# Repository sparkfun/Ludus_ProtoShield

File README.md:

**NOTE:** *This product has been retired from our catalog. If you are looking for more up-to-date info, please check out some of these resources to see how other users are still hacking and improving on this product.*
* *[SparkFun Forum](https://forum.sparkfun.com/)*
* *[Comments Here on GitHub](https://github.com/sparkfun/Ludus_ProtoShield/issues)*
* *[IRC Channel](https://www.sparkfun.com/news/263)*

SparkFun Ludus ProtoShield
===========================

[*SparkFun Ludus ProtoShield (DEV-13310)*](https://www.sparkfun.com/products/13310)

This is an Arduino shield that integrates an H-Bridge Driver and breaks out 
all I/O ports to three-pin headers on a GND / PWR / SIG standard. This enables quick
prototyping and integration of Arduino projects w/o the need of a breadboard.

Ludus is the mascot of the SparkFun Education team. It is a highly intelligent octopus.

                   _,--._
                      ,'      `.
              |\     / ,-.  ,-. \     /|
              )o),/ ( ( o )( o ) ) \.(o(
             /o/// /|  `-'  `-'  |\ \\\o\
            / / |\ \(   .    ,   )/ /| \ \
            | | \o`-/    `\/'    \-'o/ | |
            \ \  `,'              `.'  / /
         \.  \ `-'  ,'|   /\   |`.  `-' /  ,/
          \`. `.__,' /   /  \   \ `.__,' ,'/
           \o\     ,'  ,'    `.  `.     /o/
            \o`---'  ,'        `.  `---'o/
             `.____,'  -shimrod  `.____,'

Repository Contents
-------------------

* **/Firmware** - Example code 
* **/Hardware** - Eagle design files (.brd, .sch)
* **/Production** - Production panel files (.brd)

Documentation
--------------
* **[Hookup Guide](https://learn.sparkfun.com/tutorials/ludus-protoshield-hookup-guide)** - Basic hookup guide for the Ludus ProtoShield.
* **[SparkFun Fritzing repo](https://github.com/sparkfun/Fritzing_Parts)** - Fritzing diagrams for SparkFun products.
* **[SparkFun 3D Model repo](https://github.com/sparkfun/3D_Models)** - 3D models of SparkFun products. 

License Information
-------------------

This product is _**open source**_! 

Please review the LICENSE.md file for license information. 

If you have any questions or concerns on licensing, please contact techsupport@sparkfun.com.

Distributed as-is; no warranty is given.

- Your friends at SparkFun.

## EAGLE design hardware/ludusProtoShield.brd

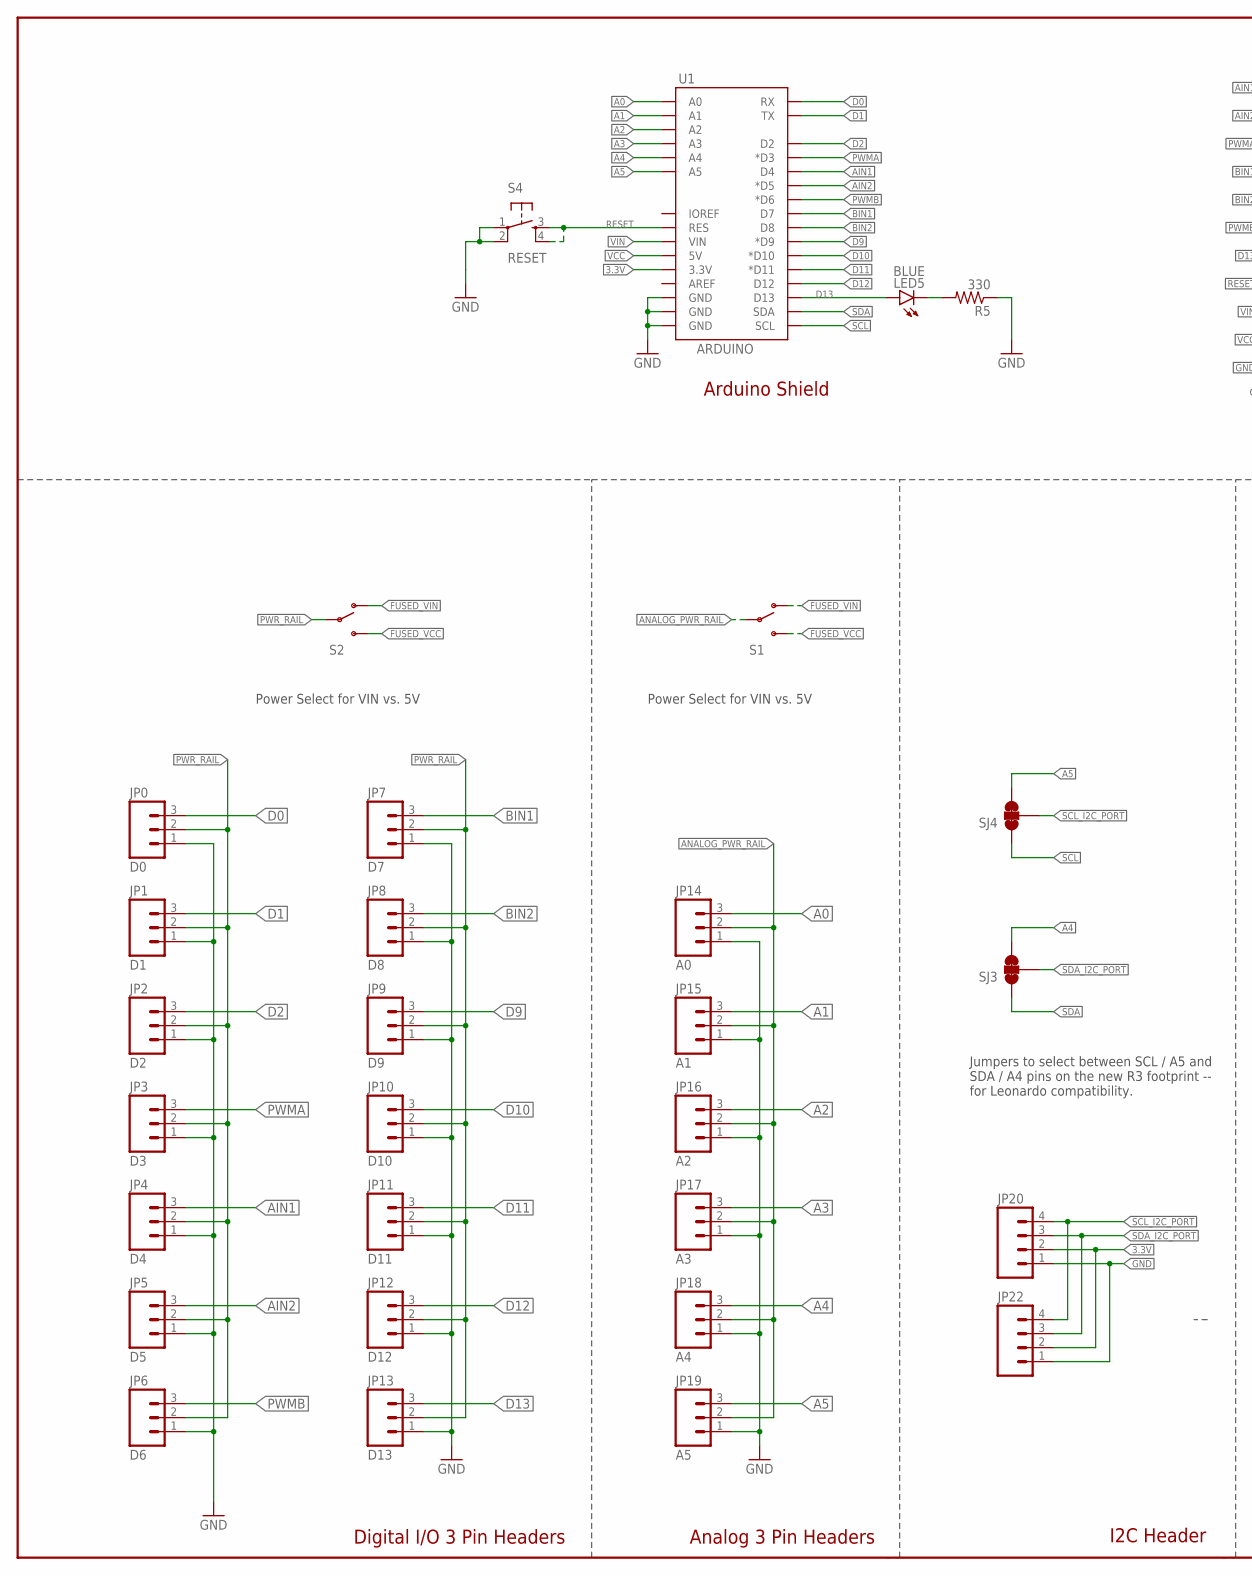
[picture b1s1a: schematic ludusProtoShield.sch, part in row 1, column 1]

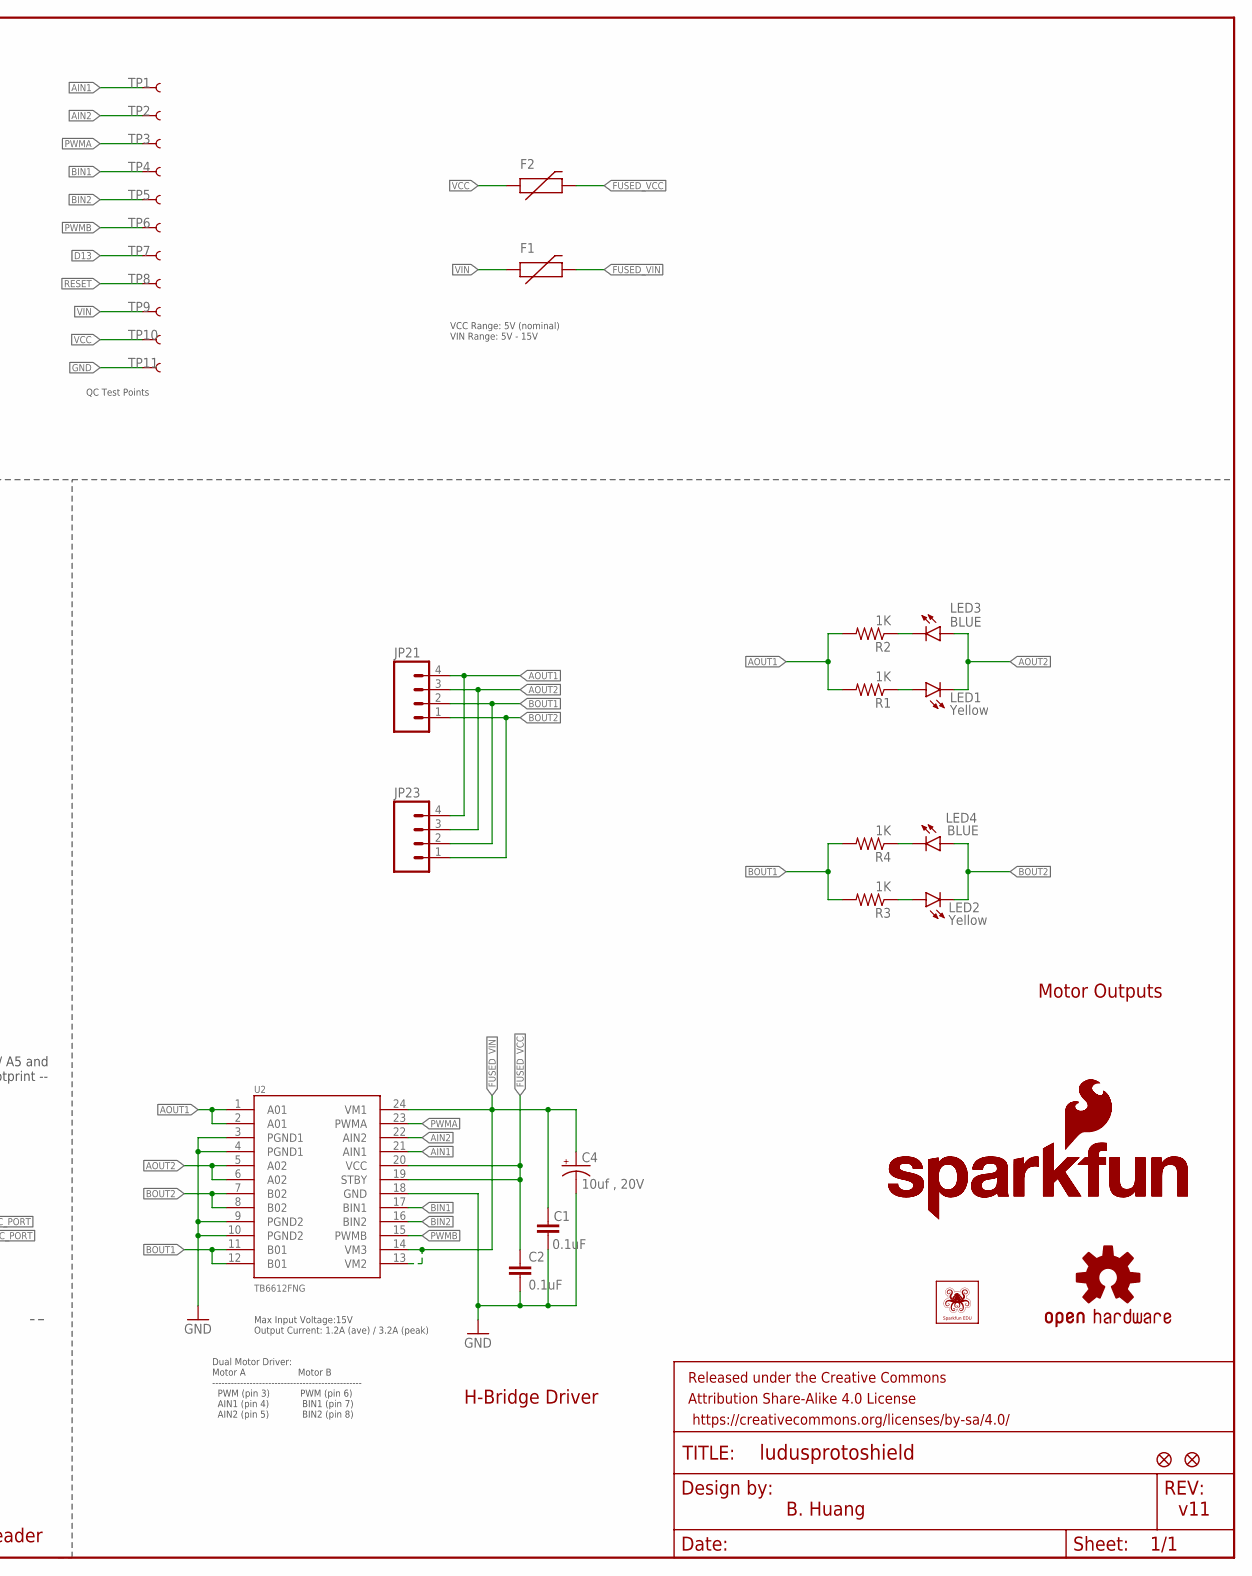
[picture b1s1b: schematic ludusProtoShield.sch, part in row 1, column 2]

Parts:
C1, C2: 0.1uF; 0603-CAP
C4: 10uf , 20V; EIA3528
F1, F2: PTCSMD; PTC-1206
FID1, FID2: FIDUCIAL1X2; FIDUCIAL-1X2
FRAME2: FRAME-LEDGER; CREATIVE_COMMONS
JP0: D0; 1X03_LOCK
JP1: D1; 1X03_LOCK
JP2: D2; 1X03_LOCK
JP3: D3; 1X03_LOCK
JP4: D4; 1X03_LOCK
JP5: D5; 1X03_LOCK
JP6: D6; 1X03_LOCK
JP7: D7; 1X03_LOCK
JP8: D8; 1X03_LOCK
JP9: D9; 1X03_LOCK
JP10: D10; 1X03_LOCK
JP11: D11; 1X03_LOCK
JP12: D12; 1X03_LOCK
JP13: D13; 1X03_LOCK
JP14: A0; 1X03_LOCK
JP15: A1; 1X03_LOCK
JP16: A2; 1X03_LOCK
JP17: A3; 1X03_LOCK
JP18: A4; 1X03_LOCK
JP19: A5; 1X03_LOCK
JP20, JP21: M04PTH; 1X04
JP22, JP23: M04LOCK; 1X04_LOCK
LED1, LED2: Yellow; LED-0603
LED3, LED4, LED5: BLUE; LED-0603
LOGO1: OSHW-LOGOM; OSHW-LOGO-M
LOGO2, LOGO4: SFE_LOGO_NAME_FLAME.1_INCH; SFE_LOGO_NAME_FLAME_.1
LOGO3: SFE_LOGO_FLAME.2COP; SFE_LOGO_FLAME_COPPER_.2
R1, R2, R3, R4: 1K; 0603-RES
R5: 330; 0603-RES
S1, S2: SWITCH-SPDTSMD; AYZ0202
S4: RESET; TACTILE-SWITCH-SMD
SJ3, SJ4: JUMPER-PAD-3-NC_BY_TRACE; PAD-JUMPER-3-3OF3_NC_BY_TRACE_YES_SILK_FULL_BOX
TP1, TP2, TP3, TP4, TP5, TP6, TP7, TP8, TP9, TP10, TP11: TEST-POINT3X5; PAD.03X.05
U1: ARDUINO; UNO_R3_SHIELD_NOLABELS_LOCK
U2: TB6612FNG; SSOP24
U$1: SFE_LUDUSSFE_LUDUS-M; SFE_LUDUS-M

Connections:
3.3V: JP20.2, JP22.2, U1.3.3V
A0: JP14.3, U1.A0
A1: JP15.3, U1.A1
A2: JP16.3, U1.A2
A3: JP17.3, U1.A3
A4: JP18.3, SJ3.3, U1.A4
A5: JP19.3, SJ4.3, U1.A5
AIN1: JP4.3, TP1.P$1, U1.D4, U2.21 (AIN1)
AIN2: JP5.3, TP2.P$1, U1.D5 (*D5), U2.22 (AIN2)
ANALOG_PWR_RAIL: JP14.2, JP15.2, JP16.2, JP17.2, JP18.2, JP19.2, S1.2
AOUT1: JP21.4, JP23.4, R1.2, R2.2, U2.1 (A01), U2.2 (A01)
AOUT2: JP21.3, JP23.3, LED1.C, LED3.A, U2.5 (A02), U2.6 (A02)
BIN1: JP7.3, TP4.P$1, U1.D7, U2.17 (BIN1)
BIN2: JP8.3, TP5.P$1, U1.D8, U2.16 (BIN2)
BOUT1: JP21.2, JP23.2, R3.2, R4.2, U2.11 (B01), U2.12 (B01)
BOUT2: JP21.1, JP23.1, LED2.C, LED4.A, U2.7 (B02), U2.8 (B02)
D0: JP0.3, U1.RX
D1: JP1.3, U1.TX
D2: JP2.3, U1.D2
D9: JP9.3, U1.D9 (*D9)
D10: JP10.3, U1.D10 (*D10)
D11: JP11.3, U1.D11 (*D11)
D12: JP12.3, U1.D12
D13: JP13.3, LED5.A, TP7.P$1, U1.D13
FUSED_VCC: C2.1, F2.2, S1.3 (S), S2.3 (S), U2.19 (STBY), U2.20 (VCC)
FUSED_VIN: C1.1, C4.A (+), F1.2, S1.1 (O), S2.1 (O), U2.13 (VM2), U2.14 (VM3), U2.24 (VM1)
GND: C1.2, C2.2, C4.C (-), JP0.1, JP1.1, JP2.1, JP3.1, JP4.1, JP5.1, JP6.1, JP7.1, JP8.1, JP9.1, JP10.1, JP11.1, JP12.1, JP13.1, JP14.1, JP15.1, JP16.1, JP17.1, JP18.1, JP19.1, JP20.1, JP22.1, R5.1, S4.1, S4.2, TP11.P$1, U1.GND@0 (GND), U1.GND@1 (GND), U1.GND@2 (GND), U2.3 (PGND1), U2.4 (PGND1), U2.9 (PGND2), U2.10 (PGND2), U2.18 (GND)
unnamed: LED5.C, R5.2
unnamed: LED1.A, R1.1
unnamed: LED3.C, R2.1
unnamed: LED2.A, R3.1
unnamed: LED4.C, R4.1
PWMA: JP3.3, TP3.P$1, U1.D3 (*D3), U2.23 (PWMA)
PWMB: JP6.3, TP6.P$1, U1.D6 (*D6), U2.15 (PWMB)
PWR_RAIL: JP0.2, JP1.2, JP2.2, JP3.2, JP4.2, JP5.2, JP6.2, JP7.2, JP8.2, JP9.2, JP10.2, JP11.2, JP12.2, JP13.2, S2.2
RESET: S4.3, S4.4, TP8.P$1, U1.RES
SCL: SJ4.1, U1.SCL
SCL_I2C_PORT: JP20.4, JP22.4, SJ4.2
SDA: SJ3.1, U1.SDA
SDA_I2C_PORT: JP20.3, JP22.3, SJ3.2
VCC: F2.1, TP10.P$1, U1.5V
VIN: F1.1, TP9.P$1, U1.VIN

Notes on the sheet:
Arduino Shield
H-Bridge Driver
I2C Header
Motor Outputs
B. Huang
v11
Digital I/O 3 Pin Headers
Analog 3 Pin Headers
Jumpers to select between SCL / A5 and SDA / A4 pins on the new R3 footprint -- for Leonardo compatibility.
Power Select for VIN vs. 5V
VCC Range: 5V (nominal) VIN Range: 5V - 15V
QC Test Points
Dual Motor Driver: Motor A Motor B ------------------------------------------------ PWM (pin 3) PWM (pin 6) AIN1 (pin 4) BIN1 (pin 7) AIN2 (pin 5) BIN2 (pin 8)
Max Input Voltage:15V Output Current: 1.2A (ave) / 3.2A (peak)

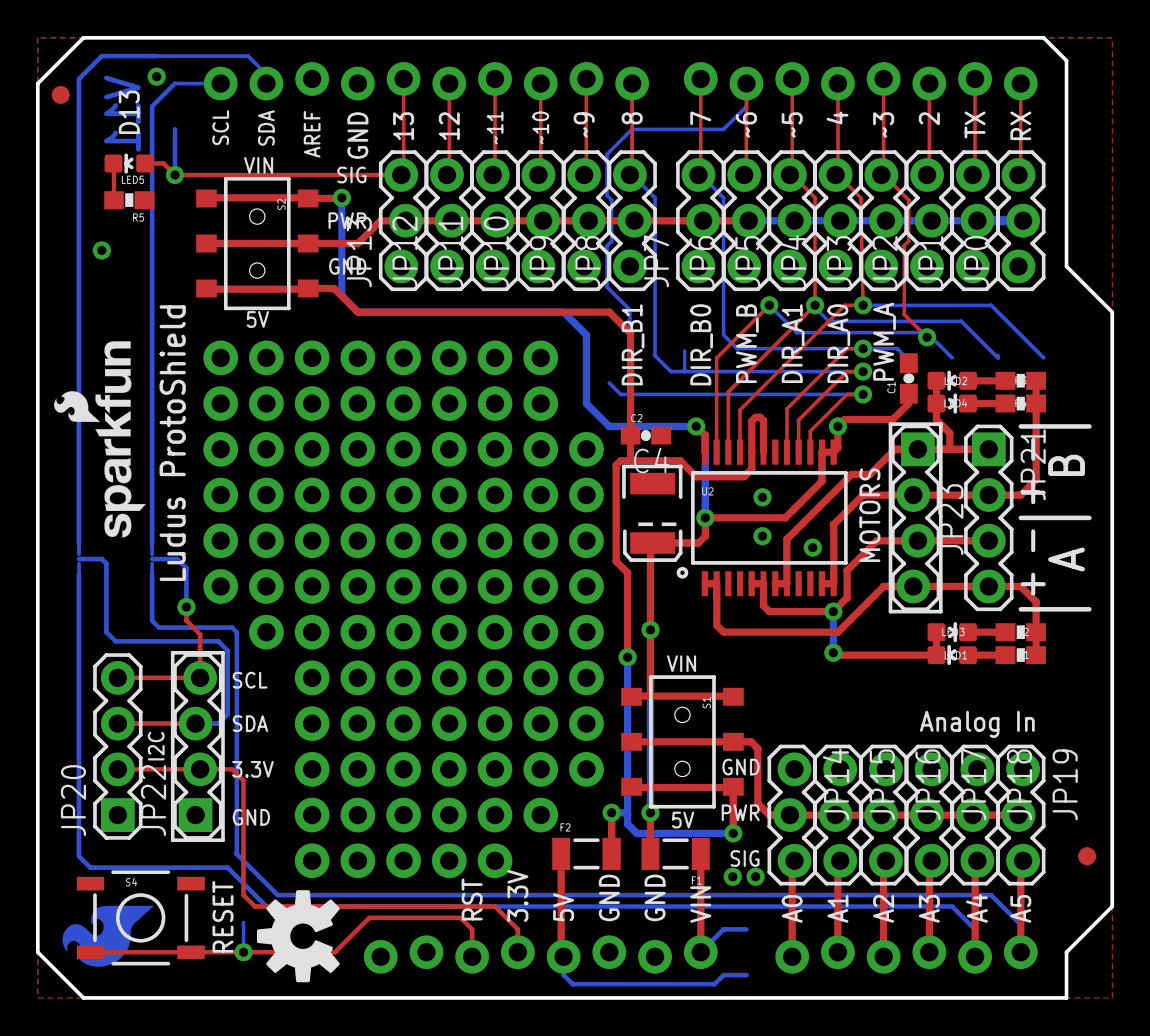
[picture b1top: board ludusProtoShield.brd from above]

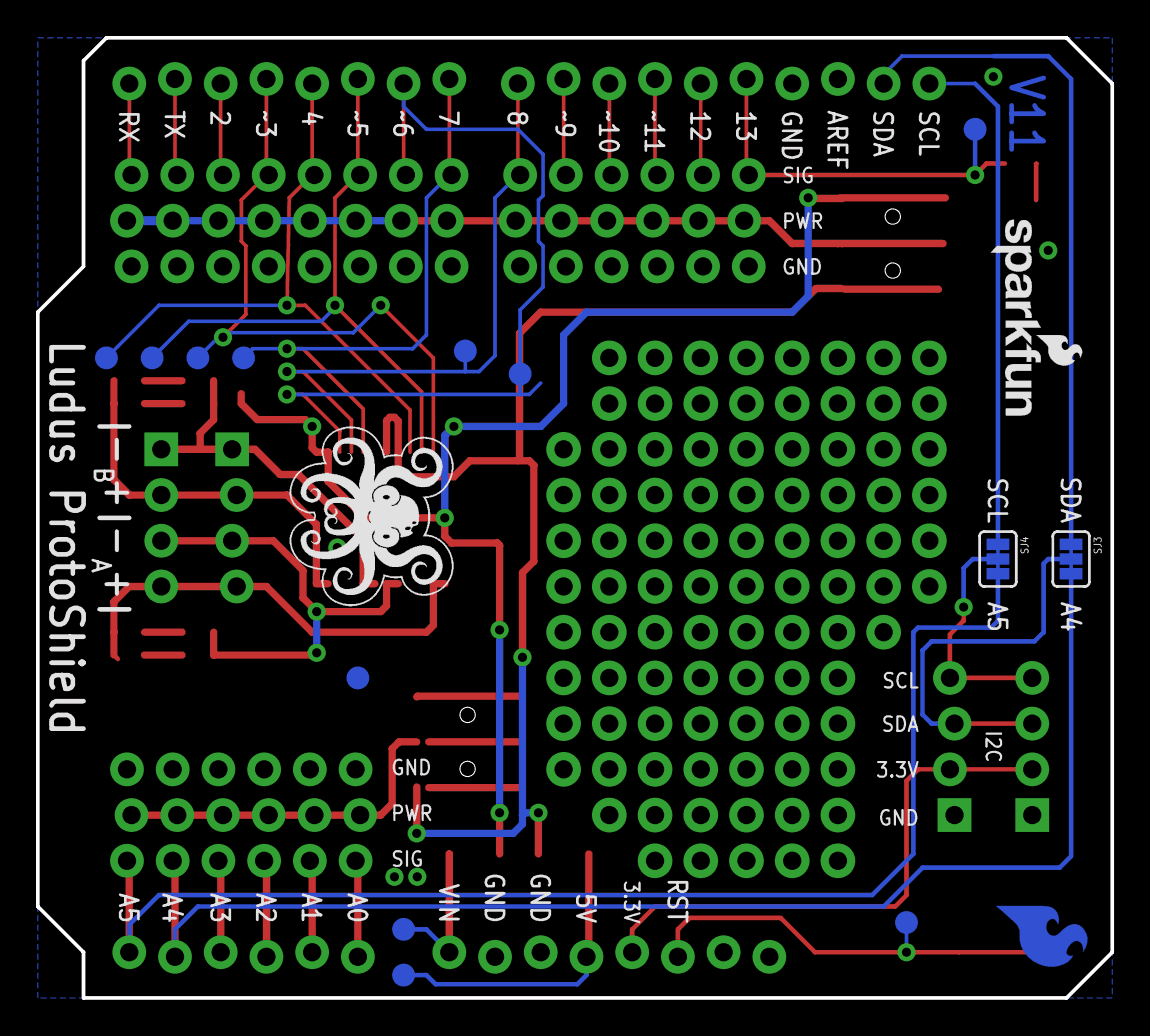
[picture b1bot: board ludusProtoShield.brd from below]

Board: 2 copper layers, 59.7 x 53.3 mm, 65 parts (16 on the bottom side), 42 nets.

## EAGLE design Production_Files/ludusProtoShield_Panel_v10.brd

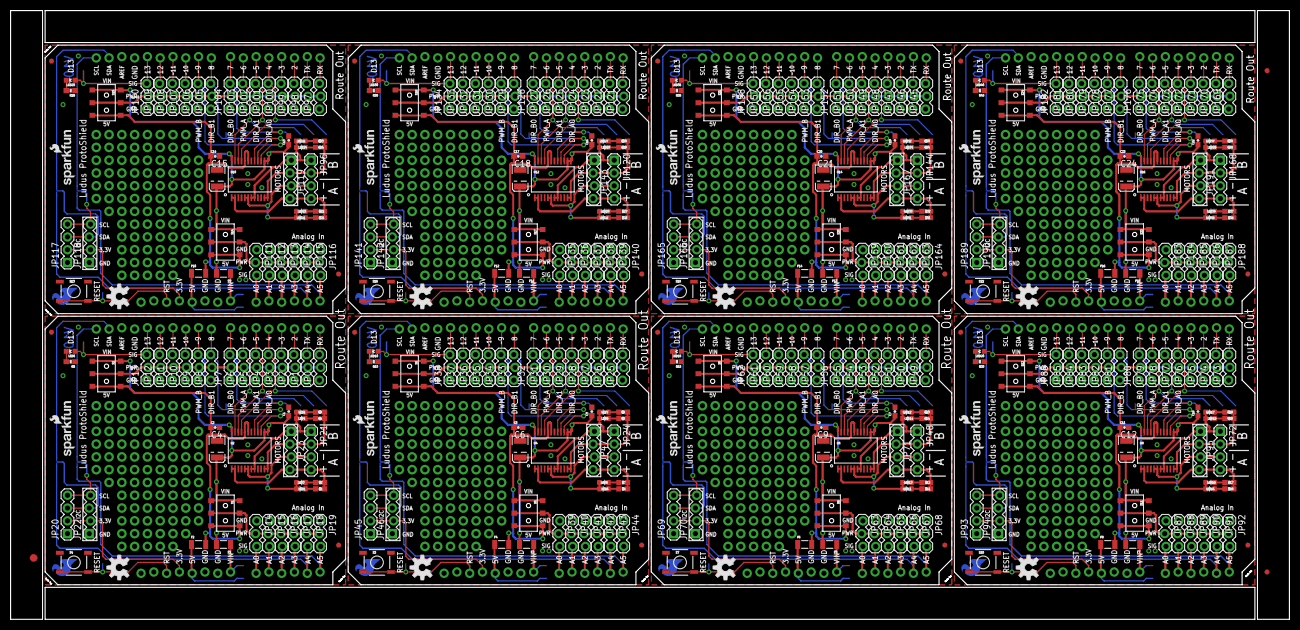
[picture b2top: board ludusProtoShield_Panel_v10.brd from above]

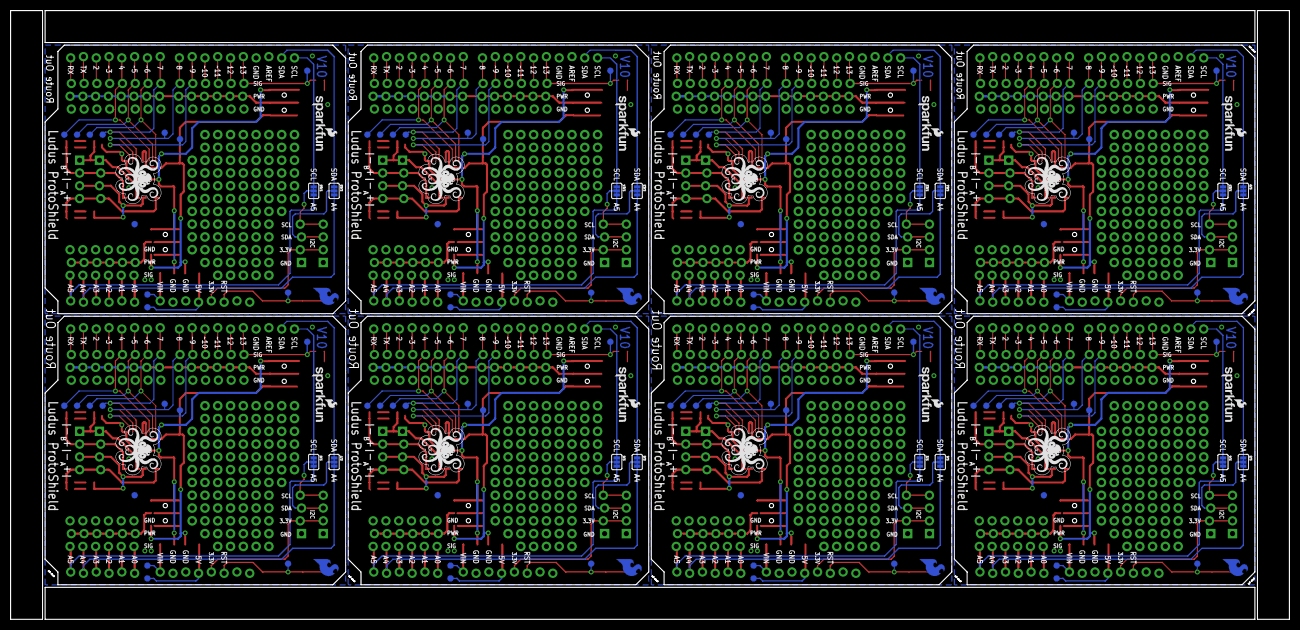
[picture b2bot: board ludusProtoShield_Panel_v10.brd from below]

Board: 2 copper layers, 254.0 x 120.9 mm, 515 parts (128 on the bottom side), 336 nets.

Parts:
C1, C2, C3, C5, C7, C8, C10, C11, C13, C14, C16, C17, C19, C20, C22, C23: 0.1uF; 0603-CAP
C4, C6, C9, C12, C15, C18, C21, C24: 10uf , 20V; EIA3528
E$1: FIDUCIAL-1.5X3
E$4, E$5: FIDUCIAL-1X2
F1, F2, F3, F4, F5, F6, F7, F8, F9, F10, F11, F12, F13, F14, F15, F16: PTC-1206
FID1, FID2, FID3, FID4, FID5, FID6, FID7, FID8, FID9, FID10, FID11, FID12, FID13, FID14, FID15, FID16: FIDUCIAL1X2; FIDUCIAL-1X2
JP0, JP25, JP49, JP73, JP97, JP121, JP145, JP169: D0; 1X03_LOCK
JP1, JP26, JP50, JP74, JP98, JP122, JP146, JP170: D1; 1X03_LOCK
JP2, JP27, JP51, JP75, JP99, JP123, JP147, JP171: D2; 1X03_LOCK
JP3, JP28, JP52, JP76, JP100, JP124, JP148, JP172: D3; 1X03_LOCK
JP4, JP29, JP53, JP77, JP101, JP125, JP149, JP173: D4; 1X03_LOCK
JP5, JP30, JP54, JP78, JP102, JP126, JP150, JP174: D5; 1X03_LOCK
JP6, JP31, JP55, JP79, JP103, JP127, JP151, JP175: D6; 1X03_LOCK
JP7, JP32, JP56, JP80, JP104, JP128, JP152, JP176: D7; 1X03_LOCK
JP8, JP33, JP57, JP81, JP105, JP129, JP153, JP177: D8; 1X03_LOCK
JP9, JP34, JP58, JP82, JP106, JP130, JP154, JP178: D9; 1X03_LOCK
JP10, JP35, JP59, JP83, JP107, JP131, JP155, JP179: D10; 1X03_LOCK
JP11, JP36, JP60, JP84, JP108, JP132, JP156, JP180: D11; 1X03_LOCK
JP12, JP37, JP61, JP85, JP109, JP133, JP157, JP181: D12; 1X03_LOCK
JP13, JP38, JP62, JP86, JP110, JP134, JP158, JP182: D13; 1X03_LOCK
JP14, JP39, JP63, JP87, JP111, JP135, JP159, JP183: A0; 1X03_LOCK
JP15, JP40, JP64, JP88, JP112, JP136, JP160, JP184: A1; 1X03_LOCK
JP16, JP41, JP65, JP89, JP113, JP137, JP161, JP185: A2; 1X03_LOCK
JP17, JP42, JP66, JP90, JP114, JP138, JP162, JP186: A3; 1X03_LOCK
JP18, JP43, JP67, JP91, JP115, JP139, JP163, JP187: A4; 1X03_LOCK
JP19, JP44, JP68, JP92, JP116, JP140, JP164, JP188: A5; 1X03_LOCK
JP20, JP21, JP24, JP45, JP48, JP69, JP72, JP93, JP96, JP117, JP120, JP141, JP144, JP165, JP168, JP189: 1X04
JP22, JP23, JP46, JP47, JP70, JP71, JP94, JP95, JP118, JP119, JP142, JP143, JP166, JP167, JP190, JP191: 1X04_LOCK
LED1, LED2, LED6, LED7, LED11, LED12, LED16, LED17, LED21, LED22, LED26, LED27, LED31, LED32, LED36, LED37: Yellow; LED-0603
LED3, LED4, LED5, LED8, LED9, LED10, LED13, LED14, LED15, LED18, LED19, LED20, LED23, LED24, LED25, LED28, LED29, LED30, LED33, LED34, LED35, LED38, LED39, LED40: BLUE; LED-0603
LOGO1, LOGO5, LOGO9, LOGO13, LOGO17, LOGO21, LOGO25, LOGO29: OSHW-LOGOM; OSHW-LOGO-M
LOGO2, LOGO4, LOGO6, LOGO7, LOGO10, LOGO11, LOGO14, LOGO15, LOGO18, LOGO19, LOGO22, LOGO23, LOGO26, LOGO27, LOGO30, LOGO31: SFE_LOGO_NAME_FLAME.1_INCH; SFE_LOGO_NAME_FLAME_.1
LOGO3, LOGO8, LOGO12, LOGO16, LOGO20, LOGO24, LOGO28, LOGO32: SFE_LOGO_FLAME.2COP; SFE_LOGO_FLAME_COPPER_.2
R1, R2, R3, R4, R6, R7, R8, R9, R11, R12, R13, R14, R16, R17, R18, R19, R21, R22, R23, R24, R26, R27, R28, R29, R31, R32, R33, R34, R36, R37, R38, R39: 1K; 0603-RES
R5, R10, R15, R20, R25, R30, R35, R40: 330; 0603-RES
S1, S2, S5, S6, S8, S9, S11, S12, S14, S15, S17, S18, S20, S21, S23, S24: AYZ0202
S3, S4, S7, S10, S13, S16, S19, S22: RESET; TACTILE-SWITCH-SMD
SJ1, SJ2, SJ3, SJ4, SJ5, SJ6, SJ7, SJ8, SJ9, SJ10, SJ11, SJ12, SJ13, SJ14, SJ15, SJ16: PAD-JUMPER-3-3OF3_NC_BY_TRACE_YES_SILK_FULL_BOX
TP1, TP2, TP3, TP4, TP5, TP6, TP7, TP8, TP9, TP10, TP11, TP12, TP13, TP14, TP15, TP16, TP17, TP18, TP19, TP20, TP21, TP22, TP23, TP24, TP25, TP26, TP27, TP28, TP29, TP30, TP31, TP32, TP33, TP34, TP35, TP36, TP37, TP38, TP39, TP40, TP41, TP42, TP43, TP44, TP45, TP46, TP47, TP48, TP49, TP50, TP51, TP52, TP53, TP54, TP55, TP56, TP57, TP58, TP59, TP60, TP61, TP62, TP63, TP64, TP65, TP66, TP67, TP68, TP69, TP70, TP71, TP72, TP73, TP74, TP75, TP76, TP77, TP78, TP79, TP80, TP81, TP82, TP83, TP84, TP85, TP86, TP87, TP88: PAD.03X.05
U1, U3, U5, U7, U9, U11, U13, U15: ARDUINO; UNO_R3_SHIELD_NOLABELS_LOCK
U2, U4, U6, U8, U10, U12, U14, U16: TB6612FNG; SSOP24
U$1, U$2, U$3, U$4, U$5, U$6, U$7, U$8: SFE_LUDUSSFE_LUDUS-M; SFE_LUDUS-M

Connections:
3.3V: JP20.2, JP22.2, U1.3.3V
3.3V1: JP45.2, JP46.2, U3.3.3V
3.3V2: JP69.2, JP70.2, U5.3.3V
3.3V3: JP93.2, JP94.2, U7.3.3V
3.3V4: JP117.2, JP118.2, U9.3.3V
3.3V5: JP141.2, JP142.2, U11.3.3V
3.3V6: JP165.2, JP166.2, U13.3.3V
3.3V7: JP189.2, JP190.2, U15.3.3V
A0: JP14.3, U1.A0
A1: JP15.3, U1.A1
A2: JP16.3, U1.A2
A3: JP17.3, U1.A3
A4: JP18.3, SJ3.3, U1.A4
A5: JP19.3, SJ4.3, U1.A5
A6: JP44.3, SJ2.3, U3.A5
A7: JP43.3, SJ1.3, U3.A4
A8: JP41.3, U3.A2
A9: JP40.3, U3.A1
A10: JP39.3, U3.A0
A11: JP42.3, U3.A3
A12: JP68.3, SJ6.3, U5.A5
A13: JP67.3, SJ5.3, U5.A4
A14: JP65.3, U5.A2
A15: JP64.3, U5.A1
A16: JP63.3, U5.A0
A17: JP66.3, U5.A3
A18: JP92.3, SJ8.3, U7.A5
A19: JP91.3, SJ7.3, U7.A4
A20: JP89.3, U7.A2
A21: JP88.3, U7.A1
A22: JP87.3, U7.A0
A23: JP90.3, U7.A3
A24: JP116.3, SJ10.3, U9.A5
A25: JP115.3, SJ9.3, U9.A4
A26: JP113.3, U9.A2
A27: JP112.3, U9.A1
A28: JP111.3, U9.A0
A29: JP114.3, U9.A3
A30: JP140.3, SJ12.3, U11.A5
A31: JP139.3, SJ11.3, U11.A4
A32: JP137.3, U11.A2
A33: JP136.3, U11.A1
A34: JP135.3, U11.A0
A35: JP138.3, U11.A3
A36: JP164.3, SJ14.3, U13.A5
A37: JP163.3, SJ13.3, U13.A4
A38: JP161.3, U13.A2
A39: JP160.3, U13.A1
A40: JP159.3, U13.A0
A41: JP162.3, U13.A3
A42: JP188.3, SJ16.3, U15.A5
A43: JP187.3, SJ15.3, U15.A4
A44: JP185.3, U15.A2
A45: JP184.3, U15.A1
A46: JP183.3, U15.A0
A47: JP186.3, U15.A3
AIN1: JP4.3, TP1.P$1, U1.D4, U2.21
AIN2: JP5.3, TP2.P$1, U1.D5, U2.22
AIN3: JP30.3, TP12.P$1, U3.D5, U4.22
AIN4: JP29.3, TP13.P$1, U3.D4, U4.21
AIN5: JP54.3, TP23.P$1, U5.D5, U6.22
AIN6: JP53.3, TP24.P$1, U5.D4, U6.21
AIN7: JP78.3, TP34.P$1, U7.D5, U8.22
AIN8: JP77.3, TP35.P$1, U7.D4, U8.21
AIN9: JP102.3, TP45.P$1, U9.D5, U10.22
AIN10: JP101.3, TP46.P$1, U9.D4, U10.21
AIN11: JP126.3, TP56.P$1, U11.D5, U12.22
AIN12: JP125.3, TP57.P$1, U11.D4, U12.21
AIN13: JP150.3, TP67.P$1, U13.D5, U14.22
AIN14: JP149.3, TP68.P$1, U13.D4, U14.21
AIN15: JP174.3, TP78.P$1, U15.D5, U16.22
AIN16: JP173.3, TP79.P$1, U15.D4, U16.21
ANALOG_PWR_RAIL: JP14.2, JP15.2, JP16.2, JP17.2, JP18.2, JP19.2, S1.2
ANALOG_PWR_RAIL1: JP39.2, JP40.2, JP41.2, JP42.2, JP43.2, JP44.2, S5.2
ANALOG_PWR_RAIL2: JP63.2, JP64.2, JP65.2, JP66.2, JP67.2, JP68.2, S8.2
ANALOG_PWR_RAIL3: JP87.2, JP88.2, JP89.2, JP90.2, JP91.2, JP92.2, S11.2
ANALOG_PWR_RAIL4: JP111.2, JP112.2, JP113.2, JP114.2, JP115.2, JP116.2, S14.2
ANALOG_PWR_RAIL5: JP135.2, JP136.2, JP137.2, JP138.2, JP139.2, JP140.2, S17.2
ANALOG_PWR_RAIL6: JP159.2, JP160.2, JP161.2, JP162.2, JP163.2, JP164.2, S20.2
ANALOG_PWR_RAIL7: JP183.2, JP184.2, JP185.2, JP186.2, JP187.2, JP188.2, S23.2
AOUT1: JP21.4, JP23.4, R1.2, R2.2, U2.1, U2.2
AOUT2: JP21.3, JP23.3, LED1.C, LED3.A, U2.5, U2.6
AOUT3: JP24.4, JP47.4, R6.2, R7.2, U4.1, U4.2
AOUT4: JP24.3, JP47.3, LED6.C, LED8.A, U4.5, U4.6
AOUT5: JP48.4, JP71.4, R11.2, R12.2, U6.1, U6.2
AOUT6: JP48.3, JP71.3, LED11.C, LED13.A, U6.5, U6.6
AOUT7: JP72.4, JP95.4, R16.2, R17.2, U8.1, U8.2
AOUT8: JP72.3, JP95.3, LED16.C, LED18.A, U8.5, U8.6
AOUT9: JP96.4, JP119.4, R21.2, R22.2, U10.1, U10.2
AOUT10: JP96.3, JP119.3, LED21.C, LED23.A, U10.5, U10.6
AOUT11: JP120.4, JP143.4, R26.2, R27.2, U12.1, U12.2
AOUT12: JP120.3, JP143.3, LED26.C, LED28.A, U12.5, U12.6
AOUT13: JP144.4, JP167.4, R31.2, R32.2, U14.1, U14.2
AOUT14: JP144.3, JP167.3, LED31.C, LED33.A, U14.5, U14.6
AOUT15: JP168.4, JP191.4, R36.2, R37.2, U16.1, U16.2
AOUT16: JP168.3, JP191.3, LED36.C, LED38.A, U16.5, U16.6
BIN1: JP7.3, TP4.P$1, U1.D7, U2.17
BIN2: JP8.3, TP5.P$1, U1.D8, U2.16
BIN3: JP32.3, TP16.P$1, U3.D7, U4.17
BIN4: JP33.3, TP17.P$1, U3.D8, U4.16
BIN5: JP56.3, TP27.P$1, U5.D7, U6.17
BIN6: JP57.3, TP28.P$1, U5.D8, U6.16
BIN7: JP80.3, TP38.P$1, U7.D7, U8.17
BIN8: JP81.3, TP39.P$1, U7.D8, U8.16
BIN9: JP104.3, TP49.P$1, U9.D7, U10.17
BIN10: JP105.3, TP50.P$1, U9.D8, U10.16
BIN11: JP128.3, TP60.P$1, U11.D7, U12.17
BIN12: JP129.3, TP61.P$1, U11.D8, U12.16
BIN13: JP152.3, TP71.P$1, U13.D7, U14.17
BIN14: JP153.3, TP72.P$1, U13.D8, U14.16
BIN15: JP176.3, TP82.P$1, U15.D7, U16.17
BIN16: JP177.3, TP83.P$1, U15.D8, U16.16
BOUT1: JP21.2, JP23.2, R3.2, R4.2, U2.11, U2.12
BOUT2: JP21.1, JP23.1, LED2.C, LED4.A, U2.7, U2.8
BOUT3: JP24.1, JP47.1, LED7.C, LED9.A, U4.7, U4.8
BOUT4: JP24.2, JP47.2, R8.2, R9.2, U4.11, U4.12
BOUT5: JP48.1, JP71.1, LED12.C, LED14.A, U6.7, U6.8
BOUT6: JP48.2, JP71.2, R13.2, R14.2, U6.11, U6.12
BOUT7: JP72.1, JP95.1, LED17.C, LED19.A, U8.7, U8.8
BOUT8: JP72.2, JP95.2, R18.2, R19.2, U8.11, U8.12
BOUT9: JP96.1, JP119.1, LED22.C, LED24.A, U10.7, U10.8
BOUT10: JP96.2, JP119.2, R23.2, R24.2, U10.11, U10.12
BOUT11: JP120.1, JP143.1, LED27.C, LED29.A, U12.7, U12.8
BOUT12: JP120.2, JP143.2, R28.2, R29.2, U12.11, U12.12
BOUT13: JP144.1, JP167.1, LED32.C, LED34.A, U14.7, U14.8
BOUT14: JP144.2, JP167.2, R33.2, R34.2, U14.11, U14.12
BOUT15: JP168.1, JP191.1, LED37.C, LED39.A, U16.7, U16.8
BOUT16: JP168.2, JP191.2, R38.2, R39.2, U16.11, U16.12
D0: JP0.3, U1.RX
D1: JP1.3, U1.TX
D2: JP2.3, U1.D2
D3: JP3.3, U1.D3
D4: JP37.3, U3.D12
D5: JP38.3, LED10.A, TP18.P$1, U3.D13
D6: JP35.3, U3.D10
D7: JP27.3, U3.D2
D8: JP36.3, U3.D11
D9: JP25.3, U3.RX
D10: JP10.3, U1.D10
D11: JP11.3, U1.D11
D12: JP12.3, U1.D12
D13: JP13.3, LED5.A, TP7.P$1, U1.D13
D14: JP26.3, U3.TX
D15: JP28.3, U3.D3
D16: JP61.3, U5.D12
D17: JP62.3, LED15.A, TP29.P$1, U5.D13
D18: JP59.3, U5.D10
D19: JP51.3, U5.D2
D20: JP60.3, U5.D11
D21: JP49.3, U5.RX
D22: JP50.3, U5.TX
D23: JP52.3, U5.D3
D24: JP85.3, U7.D12
D25: JP86.3, LED20.A, TP40.P$1, U7.D13
D26: JP83.3, U7.D10
D27: JP75.3, U7.D2
D28: JP84.3, U7.D11
D29: JP73.3, U7.RX
D30: JP74.3, U7.TX
D31: JP76.3, U7.D3
D32: JP109.3, U9.D12
D33: JP110.3, LED25.A, TP51.P$1, U9.D13
D34: JP107.3, U9.D10
D35: JP99.3, U9.D2
D36: JP108.3, U9.D11
D37: JP97.3, U9.RX
D38: JP98.3, U9.TX
D39: JP100.3, U9.D3
D40: JP133.3, U11.D12
D41: JP134.3, LED30.A, TP62.P$1, U11.D13
D42: JP131.3, U11.D10
D43: JP123.3, U11.D2
D44: JP132.3, U11.D11
D45: JP121.3, U11.RX
D46: JP122.3, U11.TX
D47: JP124.3, U11.D3
D48: JP157.3, U13.D12
D49: JP158.3, LED35.A, TP73.P$1, U13.D13
D50: JP155.3, U13.D10
D51: JP147.3, U13.D2
D52: JP156.3, U13.D11
D53: JP145.3, U13.RX
D54: JP146.3, U13.TX
D55: JP148.3, U13.D3
D56: JP181.3, U15.D12
D57: JP182.3, LED40.A, TP84.P$1, U15.D13
D58: JP179.3, U15.D10
D59: JP171.3, U15.D2
D60: JP180.3, U15.D11
D61: JP169.3, U15.RX
D62: JP170.3, U15.TX
D63: JP172.3, U15.D3
FUSED_VCC: C2.1, F2.2, S1.3, S2.3, U2.19, U2.20
FUSED_VCC1: C5.1, F4.2, S5.3, S6.3, U4.19, U4.20
FUSED_VCC2: C8.1, F6.2, S8.3, S9.3, U6.19, U6.20
FUSED_VCC3: C11.1, F8.2, S11.3, S12.3, U8.19, U8.20
FUSED_VCC4: C14.1, F10.2, S14.3, S15.3, U10.19, U10.20
FUSED_VCC5: C17.1, F12.2, S17.3, S18.3, U12.19, U12.20
FUSED_VCC6: C20.1, F14.2, S20.3, S21.3, U14.19, U14.20
FUSED_VCC7: C23.1, F16.2, S23.3, S24.3, U16.19, U16.20
FUSED_VIN: C1.1, C4.A, F1.2, S1.1, S2.1, U2.13, U2.14, U2.24
FUSED_VIN1: C3.1, C6.A, F3.2, S5.1, S6.1, U4.13, U4.14, U4.24
FUSED_VIN2: C7.1, C9.A, F5.2, S8.1, S9.1, U6.13, U6.14, U6.24
FUSED_VIN3: C10.1, C12.A, F7.2, S11.1, S12.1, U8.13, U8.14, U8.24
FUSED_VIN4: C13.1, C15.A, F9.2, S14.1, S15.1, U10.13, U10.14, U10.24
FUSED_VIN5: C16.1, C18.A, F11.2, S17.1, S18.1, U12.13, U12.14, U12.24
FUSED_VIN6: C19.1, C21.A, F13.2, S20.1, S21.1, U14.13, U14.14, U14.24
FUSED_VIN7: C22.1, C24.A, F15.2, S23.1, S24.1, U16.13, U16.14, U16.24
GND: C1.2, C2.2, C4.C, JP0.1, JP1.1, JP2.1, JP3.1, JP4.1, JP5.1, JP6.1, JP7.1, JP8.1, JP9.1, JP10.1, JP11.1, JP12.1, JP13.1, JP14.1, JP15.1, JP16.1, JP17.1, JP18.1, JP19.1, JP20.1, JP22.1, R5.1, S4.1, S4.2, TP11.P$1, U1.GND@0, U1.GND@1, U1.GND@2, U2.3, U2.4, U2.9, U2.10, U2.18
GND1: C3.2, C5.2, C6.C, JP25.1, JP26.1, JP27.1, JP28.1, JP29.1, JP30.1, JP31.1, JP32.1, JP33.1, JP34.1, JP35.1, JP36.1, JP37.1, JP38.1, JP39.1, JP40.1, JP41.1, JP42.1, JP43.1, JP44.1, JP45.1, JP46.1, R10.1, S3.1, S3.2, TP22.P$1, U3.GND@0, U3.GND@1, U3.GND@2, U4.3, U4.4, U4.9, U4.10, U4.18
GND2: C7.2, C8.2, C9.C, JP49.1, JP50.1, JP51.1, JP52.1, JP53.1, JP54.1, JP55.1, JP56.1, JP57.1, JP58.1, JP59.1, JP60.1, JP61.1, JP62.1, JP63.1, JP64.1, JP65.1, JP66.1, JP67.1, JP68.1, JP69.1, JP70.1, R15.1, S7.1, S7.2, TP33.P$1, U5.GND@0, U5.GND@1, U5.GND@2, U6.3, U6.4, U6.9, U6.10, U6.18
GND3: C10.2, C11.2, C12.C, JP73.1, JP74.1, JP75.1, JP76.1, JP77.1, JP78.1, JP79.1, JP80.1, JP81.1, JP82.1, JP83.1, JP84.1, JP85.1, JP86.1, JP87.1, JP88.1, JP89.1, JP90.1, JP91.1, JP92.1, JP93.1, JP94.1, R20.1, S10.1, S10.2, TP44.P$1, U7.GND@0, U7.GND@1, U7.GND@2, U8.3, U8.4, U8.9, U8.10, U8.18
GND4: C13.2, C14.2, C15.C, JP97.1, JP98.1, JP99.1, JP100.1, JP101.1, JP102.1, JP103.1, JP104.1, JP105.1, JP106.1, JP107.1, JP108.1, JP109.1, JP110.1, JP111.1, JP112.1, JP113.1, JP114.1, JP115.1, JP116.1, JP117.1, JP118.1, R25.1, S13.1, S13.2, TP55.P$1, U9.GND@0, U9.GND@1, U9.GND@2, U10.3, U10.4, U10.9, U10.10, U10.18
GND5: C16.2, C17.2, C18.C, JP121.1, JP122.1, JP123.1, JP124.1, JP125.1, JP126.1, JP127.1, JP128.1, JP129.1, JP130.1, JP131.1, JP132.1, JP133.1, JP134.1, JP135.1, JP136.1, JP137.1, JP138.1, JP139.1, JP140.1, JP141.1, JP142.1, R30.1, S16.1, S16.2, TP66.P$1, U11.GND@0, U11.GND@1, U11.GND@2, U12.3, U12.4, U12.9, U12.10, U12.18
GND6: C19.2, C20.2, C21.C, JP145.1, JP146.1, JP147.1, JP148.1, JP149.1, JP150.1, JP151.1, JP152.1, JP153.1, JP154.1, JP155.1, JP156.1, JP157.1, JP158.1, JP159.1, JP160.1, JP161.1, JP162.1, JP163.1, JP164.1, JP165.1, JP166.1, R35.1, S19.1, S19.2, TP77.P$1, U13.GND@0, U13.GND@1, U13.GND@2, U14.3, U14.4, U14.9, U14.10, U14.18
GND7: C22.2, C23.2, C24.C, JP169.1, JP170.1, JP171.1, JP172.1, JP173.1, JP174.1, JP175.1, JP176.1, JP177.1, JP178.1, JP179.1, JP180.1, JP181.1, JP182.1, JP183.1, JP184.1, JP185.1, JP186.1, JP187.1, JP188.1, JP189.1, JP190.1, R40.1, S22.1, S22.2, TP88.P$1, U15.GND@0, U15.GND@1, U15.GND@2, U16.3, U16.4, U16.9, U16.10, U16.18
unnamed: LED5.C, R5.2
unnamed: LED1.A, R1.1
unnamed: LED3.C, R2.1
unnamed: LED2.A, R3.1
unnamed: LED4.C, R4.1
unnamed: LED6.A, R6.1
unnamed: LED8.C, R7.1
unnamed: LED7.A, R8.1
unnamed: LED9.C, R9.1
unnamed: LED10.C, R10.2
unnamed: LED11.A, R11.1
unnamed: LED13.C, R12.1
unnamed: LED12.A, R13.1
unnamed: LED14.C, R14.1
unnamed: LED15.C, R15.2
unnamed: LED16.A, R16.1
unnamed: LED18.C, R17.1
unnamed: LED17.A, R18.1
unnamed: LED19.C, R19.1
unnamed: LED20.C, R20.2
unnamed: LED21.A, R21.1
unnamed: LED23.C, R22.1
unnamed: LED22.A, R23.1
unnamed: LED24.C, R24.1
unnamed: LED25.C, R25.2
unnamed: LED26.A, R26.1
unnamed: LED28.C, R27.1
unnamed: LED27.A, R28.1
unnamed: LED29.C, R29.1
unnamed: LED30.C, R30.2
unnamed: LED31.A, R31.1
unnamed: LED33.C, R32.1
unnamed: LED32.A, R33.1
unnamed: LED34.C, R34.1
unnamed: LED35.C, R35.2
unnamed: LED36.A, R36.1
unnamed: LED38.C, R37.1
unnamed: LED37.A, R38.1
unnamed: LED39.C, R39.1
unnamed: LED40.C, R40.2
PWMA: JP6.3, TP3.P$1, U1.D6, U2.23
PWMA1: JP31.3, TP14.P$1, U3.D6, U4.23
PWMA2: JP55.3, TP25.P$1, U5.D6, U6.23
PWMA3: JP79.3, TP36.P$1, U7.D6, U8.23
PWMA4: JP103.3, TP47.P$1, U9.D6, U10.23
PWMA5: JP127.3, TP58.P$1, U11.D6, U12.23
PWMA6: JP151.3, TP69.P$1, U13.D6, U14.23
PWMA7: JP175.3, TP80.P$1, U15.D6, U16.23
PWMB: JP9.3, TP6.P$1, U1.D9, U2.15
PWMB1: JP34.3, TP15.P$1, U3.D9, U4.15
PWMB2: JP58.3, TP26.P$1, U5.D9, U6.15
PWMB3: JP82.3, TP37.P$1, U7.D9, U8.15
PWMB4: JP106.3, TP48.P$1, U9.D9, U10.15
PWMB5: JP130.3, TP59.P$1, U11.D9, U12.15
PWMB6: JP154.3, TP70.P$1, U13.D9, U14.15
PWMB7: JP178.3, TP81.P$1, U15.D9, U16.15
PWR_RAIL: JP0.2, JP1.2, JP2.2, JP3.2, JP4.2, JP5.2, JP6.2, JP7.2, JP8.2, JP9.2, JP10.2, JP11.2, JP12.2, JP13.2, S2.2
PWR_RAIL1: JP25.2, JP26.2, JP27.2, JP28.2, JP29.2, JP30.2, JP31.2, JP32.2, JP33.2, JP34.2, JP35.2, JP36.2, JP37.2, JP38.2, S6.2
PWR_RAIL2: JP49.2, JP50.2, JP51.2, JP52.2, JP53.2, JP54.2, JP55.2, JP56.2, JP57.2, JP58.2, JP59.2, JP60.2, JP61.2, JP62.2, S9.2
PWR_RAIL3: JP73.2, JP74.2, JP75.2, JP76.2, JP77.2, JP78.2, JP79.2, JP80.2, JP81.2, JP82.2, JP83.2, JP84.2, JP85.2, JP86.2, S12.2
PWR_RAIL4: JP97.2, JP98.2, JP99.2, JP100.2, JP101.2, JP102.2, JP103.2, JP104.2, JP105.2, JP106.2, JP107.2, JP108.2, JP109.2, JP110.2, S15.2
PWR_RAIL5: JP121.2, JP122.2, JP123.2, JP124.2, JP125.2, JP126.2, JP127.2, JP128.2, JP129.2, JP130.2, JP131.2, JP132.2, JP133.2, JP134.2, S18.2
PWR_RAIL6: JP145.2, JP146.2, JP147.2, JP148.2, JP149.2, JP150.2, JP151.2, JP152.2, JP153.2, JP154.2, JP155.2, JP156.2, JP157.2, JP158.2, S21.2
PWR_RAIL7: JP169.2, JP170.2, JP171.2, JP172.2, JP173.2, JP174.2, JP175.2, JP176.2, JP177.2, JP178.2, JP179.2, JP180.2, JP181.2, JP182.2, S24.2
RESET: S4.3, S4.4, TP8.P$1, U1.RES
RESET1: S3.3, S3.4, TP19.P$1, U3.RES
RESET2: S7.3, S7.4, TP30.P$1, U5.RES
RESET3: S10.3, S10.4, TP41.P$1, U7.RES
RESET4: S13.3, S13.4, TP52.P$1, U9.RES
RESET5: S16.3, S16.4, TP63.P$1, U11.RES
RESET6: S19.3, S19.4, TP74.P$1, U13.RES
RESET7: S22.3, S22.4, TP85.P$1, U15.RES
SCL: SJ4.1, U1.SCL
SCL1: SJ2.1, U3.SCL
SCL2: SJ6.1, U5.SCL
SCL3: SJ8.1, U7.SCL
SCL4: SJ10.1, U9.SCL
SCL5: SJ12.1, U11.SCL
SCL6: SJ14.1, U13.SCL
SCL7: SJ16.1, U15.SCL
SCL_I2C_PORT: JP20.4, JP22.4, SJ4.2
SCL_I2C_PORT1: JP45.4, JP46.4, SJ2.2
SCL_I2C_PORT2: JP69.4, JP70.4, SJ6.2
SCL_I2C_PORT3: JP93.4, JP94.4, SJ8.2
SCL_I2C_PORT4: JP117.4, JP118.4, SJ10.2
SCL_I2C_PORT5: JP141.4, JP142.4, SJ12.2
SCL_I2C_PORT6: JP165.4, JP166.4, SJ14.2
SCL_I2C_PORT7: JP189.4, JP190.4, SJ16.2
SDA: SJ3.1, U1.SDA
SDA1: SJ1.1, U3.SDA
SDA2: SJ5.1, U5.SDA
SDA3: SJ7.1, U7.SDA
SDA4: SJ9.1, U9.SDA
SDA5: SJ11.1, U11.SDA
SDA6: SJ13.1, U13.SDA
SDA7: SJ15.1, U15.SDA
SDA_I2C_PORT: JP20.3, JP22.3, SJ3.2
SDA_I2C_PORT1: JP45.3, JP46.3, SJ1.2
SDA_I2C_PORT2: JP69.3, JP70.3, SJ5.2
SDA_I2C_PORT3: JP93.3, JP94.3, SJ7.2
SDA_I2C_PORT4: JP117.3, JP118.3, SJ9.2
SDA_I2C_PORT5: JP141.3, JP142.3, SJ11.2
SDA_I2C_PORT6: JP165.3, JP166.3, SJ13.2
SDA_I2C_PORT7: JP189.3, JP190.3, SJ15.2
VCC: F2.1, TP10.P$1, U1.5V
VCC1: F4.1, TP21.P$1, U3.5V
VCC2: F6.1, TP32.P$1, U5.5V
VCC3: F8.1, TP43.P$1, U7.5V
VCC4: F10.1, TP54.P$1, U9.5V
VCC5: F12.1, TP65.P$1, U11.5V
VCC6: F14.1, TP76.P$1, U13.5V
VCC7: F16.1, TP87.P$1, U15.5V
VIN: F1.1, TP9.P$1, U1.VIN
VIN1: F3.1, TP20.P$1, U3.VIN
VIN2: F5.1, TP31.P$1, U5.VIN
VIN3: F7.1, TP42.P$1, U7.VIN
VIN4: F9.1, TP53.P$1, U9.VIN
VIN5: F11.1, TP64.P$1, U11.VIN
VIN6: F13.1, TP75.P$1, U13.VIN
VIN7: F15.1, TP86.P$1, U15.VIN

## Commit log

2015-01-09 Updated Silk and moved Motor connections
    Updated the silk name to Ludus ProtoShield and moved the motor
    connections below the SMD headers
2015-01-14 Changed SMD 4 pin female header to PTH
    Updated design to utilize the selective soldering machine and the speed
    of our PnP machine.
    Added silk to bottom layer for pins.
    Updated to v11
2015-01-15 Changed layout of shield to include staggered locking holes
2015-01-15 filename change
    Updated filename to ludusProtoShield.
    Updating the repo name to match after this commit.
2015-02-09 Updated design to resolve all issues
2015-02-09 Minor silk change
    Updated the silk to show 5V instead of VCC on power rail switch
2015-02-09 Fixed ERC & Board Consistency errors
2015-03-02 Minor silk changes
    Updated pin silks to 0.04 for all ones that don't interfere with other
    masks.
    Added to bSilk labels for the motor out
2015-03-05 Final changes to v1.0
    Final design changes from engineering design review. Ready for reds.
2015-03-30 Updated libraries and fixed issues from QC for Reds
    Updated all of the product libraries and cleaned up extra labels in
    hidden layers per issues #10-14
2015-03-30 Added QC testpoints to board
2015-03-30 Nudged test points and fixed led prod_id for led 5
    moved test points to avoid selective solder coverage and updated led 5
    to include production id.
2015-03-31 deleted old panel
2015-03-31 Updated all silk images using Pete's new artwork
    Updated all silk images using Pete's new artwork
2015-03-31 created panel v10
2015-04-13 Moved PWM control pins to 3 & 6 instead of 6 & 9
    Updated wiring to be compatible with Arduino Servo library. Updated to
    ver. 1.1
2015-04-13 Moved silk to reflect pin change
    Updated the silk for PWMA and PWMB
2015-04-14 Updates to reflect changes for Issue #17 & #18
    DRC Check: +
2015-04-14 Revert "Updates to reflect changes for Issue #17 & #18"
    This reverts commit 8485361f9dfebb0a91455fa50c213d3bada30c15.
2015-04-14 Revert "Revert "Updates to reflect changes for Issue #17 & #18""
    This reverts commit 5692900b07c6701b416bef0e24551a599566d7ad.
2015-04-16 deleted bad panel
2015-05-04 Fixed VIN 4-way junction re: Issue #19
2015-07-06 Cleaning up repo, updating .git files, updating README
2015-07-10 Cephalopod Gripe
    I removed the redundant phrase ", 8-legged (tenacled)" from the sentence explaning what Ludus is. He's an octopus, 8 is right there in the name. Also, generally speaking, octopi have 8 arms, not tent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
2015-07-10 Added Example Firmware
2015-07-30 Updating README

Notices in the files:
parts and their libraries:
SparkFun-Connectors: Licensing: CC v3.0 Share-Alike You are welcome to use this library for commercial purposes.
SparkFun-Boards: Licensing: Creative Commons ShareAlike 4.0 International - https://creativecommons.org/licenses/by-sa/4.0
SparkFun-Aesthetics: Released under the Creative Commons
